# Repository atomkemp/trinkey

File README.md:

trinkey
=======

The 32bit, Trinket based, 2 x password keeper. For build instructions check out my hackaday.io page: http://hackaday.io/project/3006-TrinKey

That'll do pig. That'll do.

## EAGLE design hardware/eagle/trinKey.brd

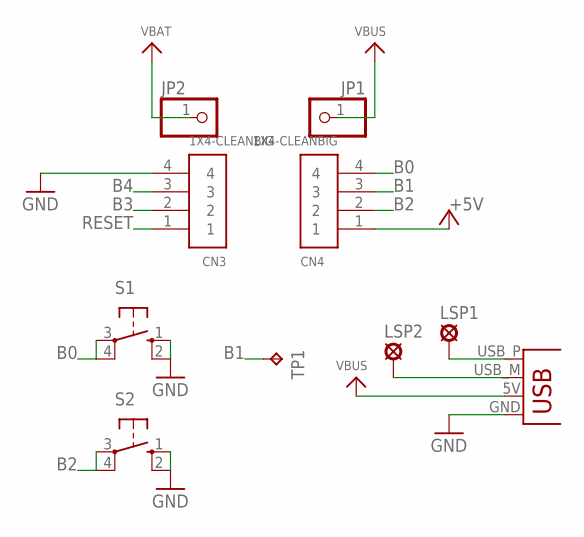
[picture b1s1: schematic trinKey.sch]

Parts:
CN3, CN4: 1X4-CLEANBIG; 1X04-CLEANBIG
JP1, JP2: PINHD-1X1CB; 1X01-CLEANBIG
JP4: USBPCB; USB-A-PCB
LSP1, LSP2: LSP10
S1, S2: 10-XX; B3F-10XX
TP1: TPB1,27; B1,27

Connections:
+5V: CN4.1
B0: CN4.4, S1.3, S1.4 (P1)
B1: CN4.3, TP1.TP
B2: CN4.2, S2.3, S2.4 (P1)
B3: CN3.2
B4: CN3.3
GND: CN3.4, JP4.GND, S1.1 (S), S1.2 (S1), S2.1 (S), S2.2 (S1)
unnamed: JP4.USB_P (D+), LSP1.MP
unnamed: JP4.USB_M (D-), LSP2.MP
RESET: CN3.1
VBAT: JP2.1
VBUS: JP1.1, JP4.5V (VBUS)

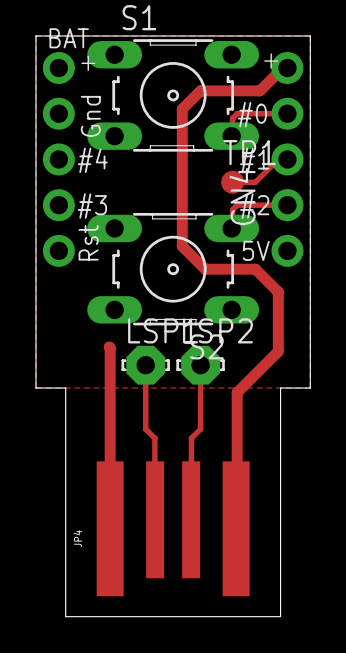
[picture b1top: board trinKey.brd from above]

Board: 2 copper layers, 15.2 x 32.3 mm, 10 parts (0 on the bottom side), 7 nets.

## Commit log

2014-09-13 initial file upload
2014-09-15 SparkKey.ino
    Modified to use on Digispark from http://digistump.com/

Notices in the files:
parts and their libraries:
SparkFun-Connectors: Licensing: Creative Commons ShareAlike 4.0 International - https://creativecommons.org/licenses/by-sa/4.0
microbuilder: This work is placed in the public domain, and may be freely used for commercial and non-commercial work with the following conditions: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
